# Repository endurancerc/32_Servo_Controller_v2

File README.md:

[README.md](https://github.com/user-attachments/files/35425972/README.md)
32 SERVO CONTROLLER V2 - THIS IS A WORK IN PROGRESS, POSTING FOR ANYONE THAT CARES

New Features in v2

\--------------------------------------------------------------------------------------------------------------------

Re-designed layout, better usb-c placement

STM32 dedicated servo driver (TRUE 12BIT RESOLUTION)

onboard microphone and stereo amplifiers

Full color TFT @ 324x240

Onboard GPS/GLONASS receiver

OV5640 camera support

microSD card slot on the bottom

onboard button pad (it broke during testing so i might scrap this pad. looks nice and had potential but too fragile)

Support for many I2C add on sensors. CO2, Air Quality, Thermal Camera, GPS

Runs DOOM and other silly games

Onboard Aircraft Tracker

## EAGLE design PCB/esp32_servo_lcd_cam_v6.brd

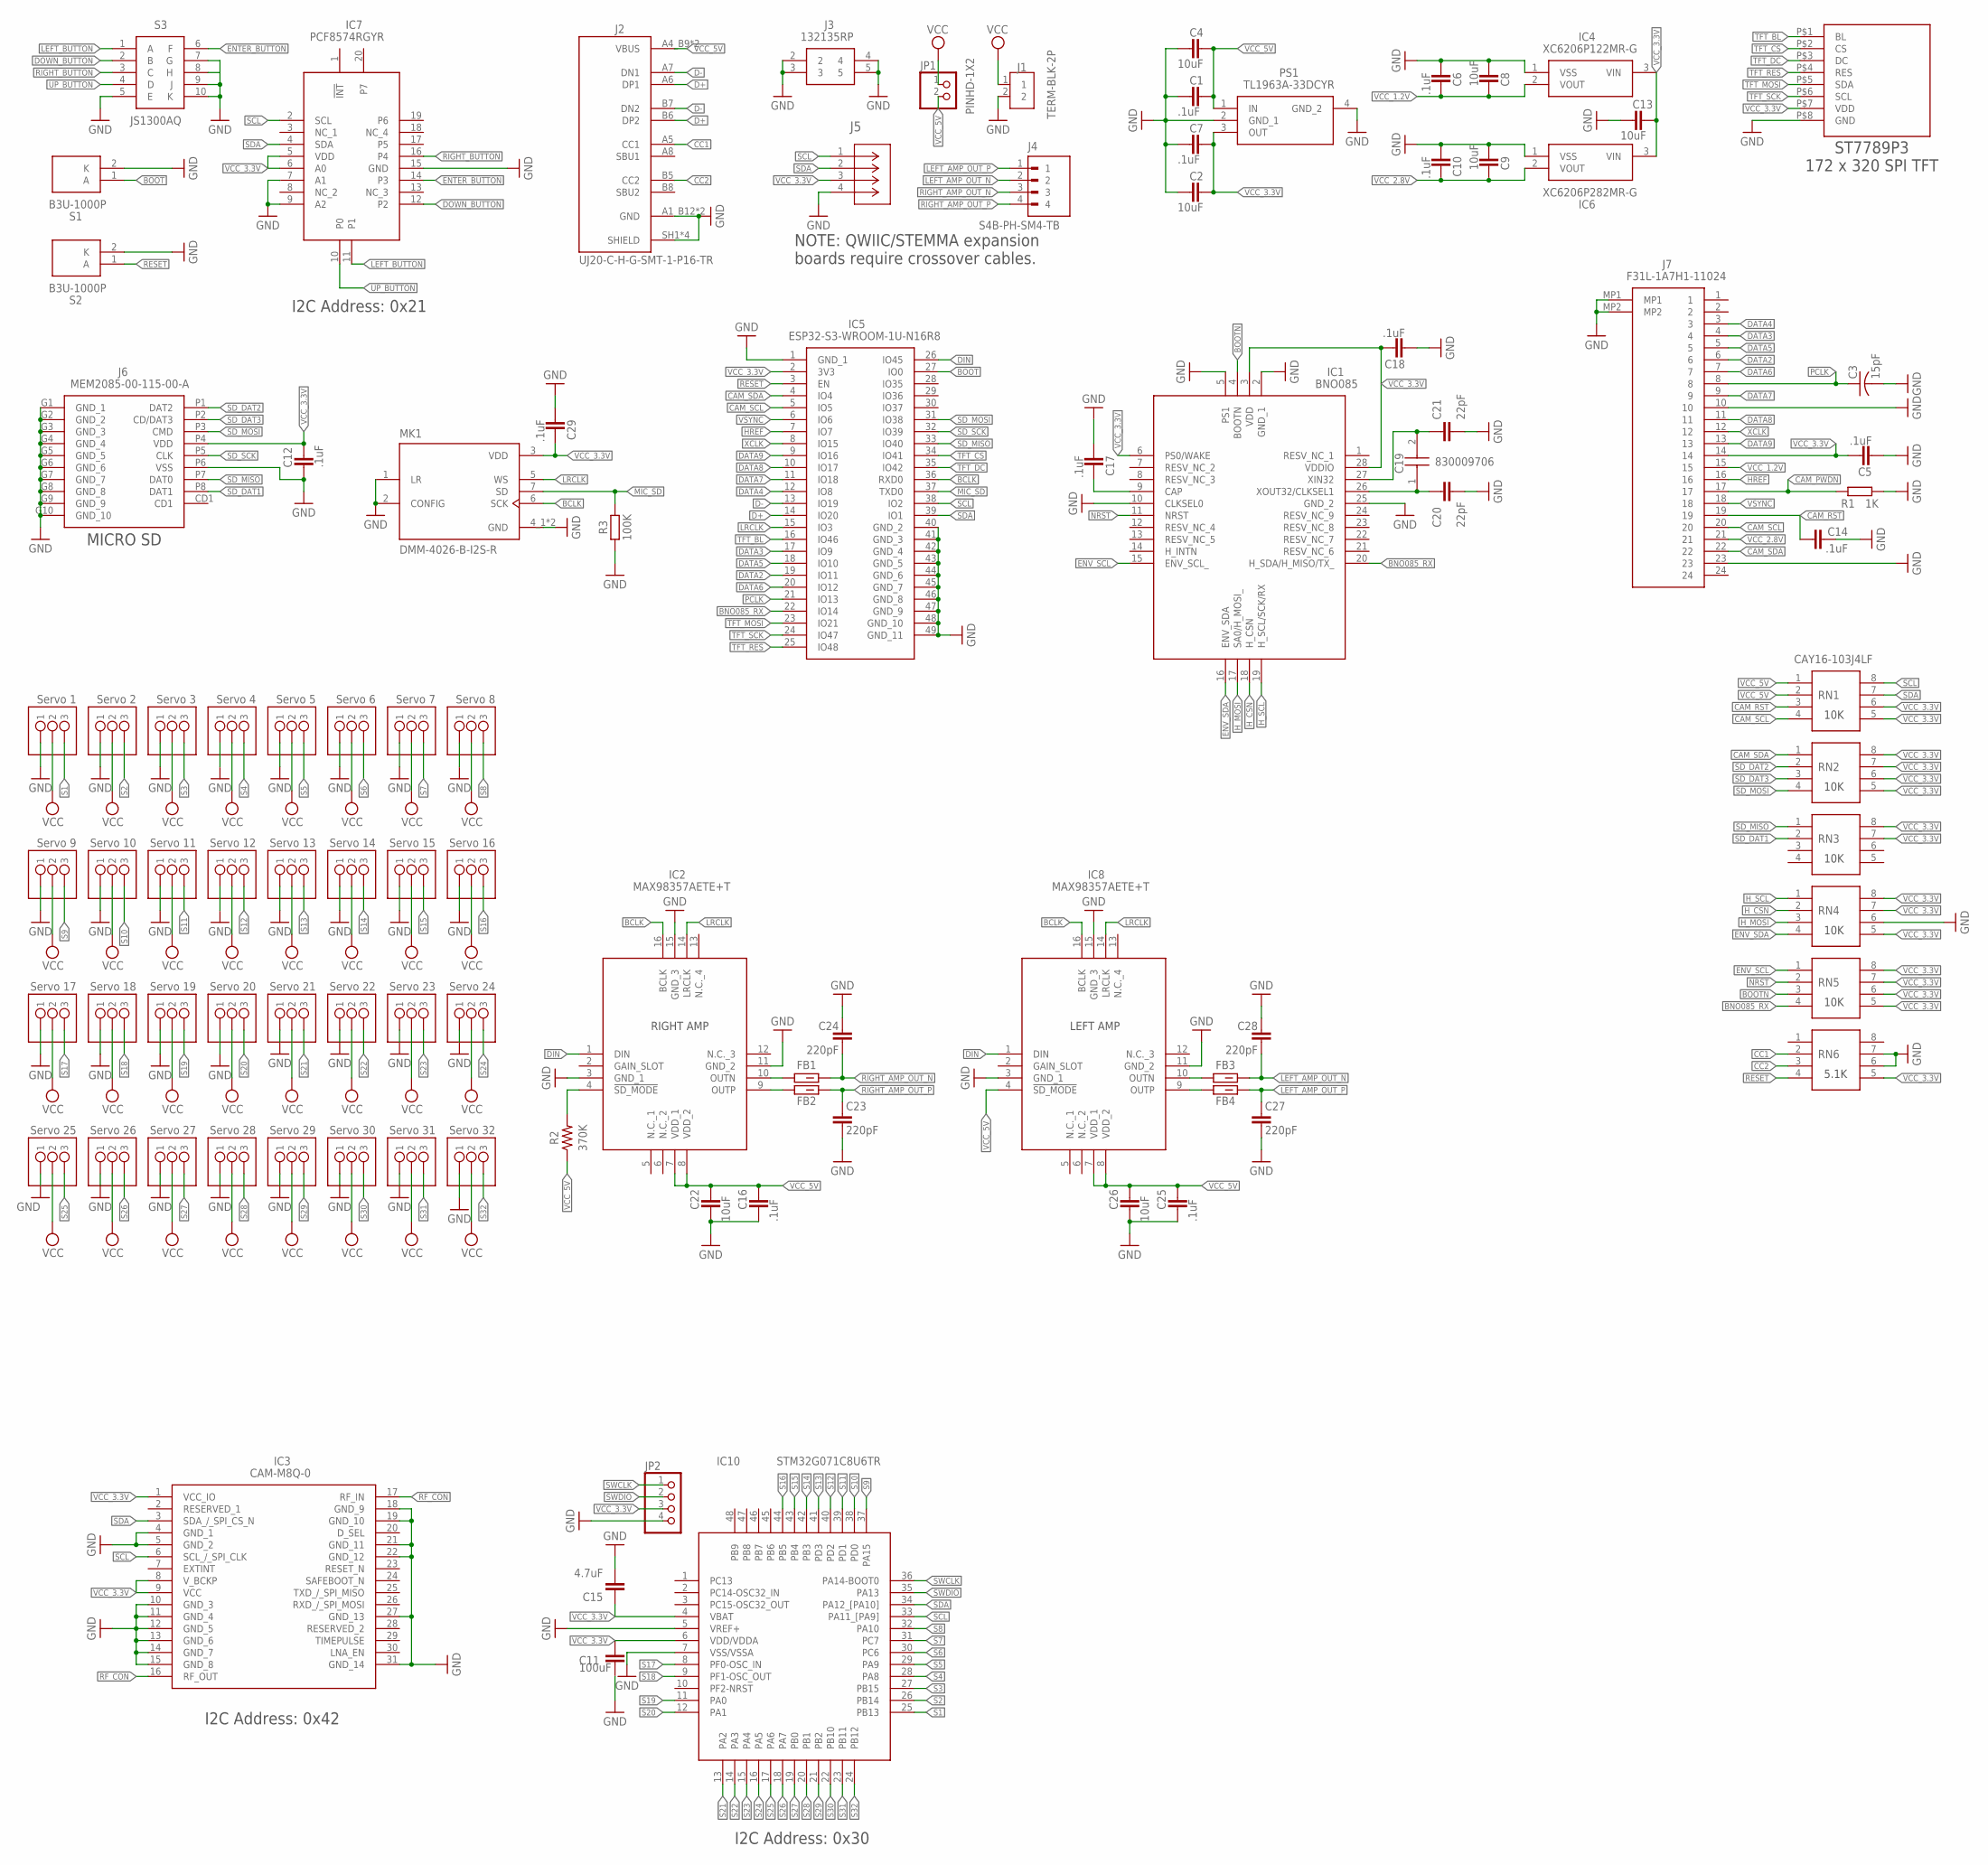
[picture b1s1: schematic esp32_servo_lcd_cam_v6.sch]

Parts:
C1, C5, C6, C7, C10, C12, C14, C16, C17, C18, C25, C29: .1uF; CAPC1110X102
C2, C4, C8, C9, C13, C22, C26: 10uF; CAPC1110X102
C3: 15pF; CAPC2012X110
C11: 100uF; CAPC3225X135
C15: 4.7uF; CAPC1005X60
C19: 830009706
C20, C21: 22pF; CAPC1005X60
C23, C24, C27, C28: 220pF; CAPC1005X60
FB1, FB2, FB3, FB4: LM18AG601; BEADC1608X95N
IC1: BNO085
IC2, IC8: MAX98357AETE+T; QFN50P300X300X80-17N
IC3: CAM-M8Q-0; CAMM8Q0
IC4: XC6206P122MR-G; SOT95P280X130-3N
IC5: ESP32-S3-WROOM-1U-N16R8; ESP32S3WROOM1UN16R8
IC6: XC6206P282MR-G; SOT95P280X130-3N
IC7: PCF8574RGYR; SN74CB3Q3244RGYR
IC10: STM32G071C8U6TR; QFN50P700X700X65-49N
J1: TERM-BLK-2P; TERMBLK_508-2N
J2: UJ20-C-H-G-SMT-1-P16-TR; SAMESKY_UJ20-C-H-G-SMT-1-P16-TR
J3: 132135RP
J4: S4B-PH-SM4-TB; JST_S4B-PH-SM4-TB
J5: SM04B-SRSS-TBCONN_SM04B-SRSS-TB_JST; CONN_SM04B-SRSS-TB_JST
J6: MEM2085-00-115-00-A; MEM20850011500A
J7: F31L-1A7H1-11024; F31L1A7H111024
JP1: PINHD-1X2; 1X02
JP2: PINHD-1X4; 1X04
MK1: DMM-4026-B-I2S-R; MIC_DMM-4026-B-I2S-R
PS1: TL1963A-33DCYR; SOT230P700X180-4N
R1: 1K; RESC1608X60
R2: 370K; RESC1608X60
R3: 100K; RESC1005X40
RN1, RN2, RN3, RN4, RN5, RN6: CAY16-103J4LF; CAY16151J4LF
S1, S2: B3U-1000P
S3: JS1300AQ; JS1300
U$1: Servo 6; 1X03
U$2: Servo 7; 1X03
U$3: Servo 8; 1X03
U$4: Servo 9; 1X03
U$5: Servo 10; 1X03
U$6: Servo 11; 1X03
U$7: Servo 12; 1X03
U$8: Servo 13; 1X03
U$9: Servo 14; 1X03
U$10: Servo 15; 1X03
U$11: Servo 4; 1X03
U$12: Servo 5; 1X03
U$13: Servo 1; 1X03
U$14: Servo 3; 1X03
U$15: Servo 2; 1X03
U$16: Servo 16; 1X03
U$17: Servo 17; 1X03
U$18: Servo 18; 1X03
U$19: Servo 19; 1X03
U$20: Servo 21; 1X03
U$21: Servo 20; 1X03
U$22: Servo 22; 1X03
U$23: Servo 23; 1X03
U$24: Servo 24; 1X03
U$25: Servo 25; 1X03
U$26: Servo 26; 1X03
U$27: Servo 27; 1X03
U$28: Servo 28; 1X03
U$29: Servo 29; 1X03
U$30: Servo 30; 1X03
U$31: Servo 31; 1X03
U$32: Servo 32; 1X03
U$33: 1.47_IN_TFT_172_320_ST7789P3

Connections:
BCLK: IC2.16 (BCLK), IC5.36 (RXD0), IC8.16 (BCLK), MK1.6 (SCK)
BNO085_RX: IC1.20 (H_SDA/H_MISO/TX_), IC5.22 (IO14), RN5.4
BOOT: IC5.27 (IO0), S1.1 (A)
BOOTN: IC1.4 (BOOTN), RN5.3
CAM_PWDN: J7.17, R1.1
CAM_RST: C14.1, J7.19, RN1.3
CAM_SCL: IC5.5 (IO5), J7.20, RN1.4
CAM_SDA: IC5.4 (IO4), J7.22, RN2.1
CC1: J2.A5 (CC1), RN6.2
CC2: J2.B5 (CC2), RN6.3
D+: IC5.14 (IO20), J2.A6 (DP1), J2.B6 (DP2)
D-: IC5.13 (IO19), J2.A7 (DN1), J2.B7 (DN2)
DATA2: IC5.19 (IO11), J7.6
DATA3: IC5.17 (IO9), J7.4
DATA4: IC5.12 (IO8), J7.3
DATA5: IC5.18 (IO10), J7.5
DATA6: IC5.20 (IO12), J7.7
DATA7: IC5.11 (IO18), J7.9
DATA8: IC5.10 (IO17), J7.11
DATA9: IC5.9 (IO16), J7.13
DIN: IC2.1 (DIN), IC5.26 (IO45), IC8.1 (DIN)
DOWN_BUTTON: IC7.12 (P2), S3.2 (B)
ENTER_BUTTON: IC7.14 (P3), S3.6 (F)
ENV_SCL: IC1.15 (ENV_SCL_), RN5.1
ENV_SDA: IC1.16 (ENV_SDA), RN4.4
GND: C1.2, C2.2, C3.2, C4.2, C5.2, C6.2, C7.2, C8.2, C9.2, C10.2, C11.2, C12.2, C13.2, C14.2, C15.2, C16.2, C17.2, C18.2, C20.2, C21.2, C22.2, C23.2, C24.2, C25.2, C26.2, C27.2, C28.2, C29.2, IC1.2 (GND_1), IC1.5 (PS1), IC1.10 (CLKSEL0), IC1.25 (GND_2), IC2.3 (GND_1), IC2.11 (GND_2), IC2.15 (GND_3), IC3.4 (GND_1), IC3.5 (GND_2), IC3.10 (GND_3), IC3.11 (GND_4), IC3.12 (GND_5), IC3.13 (GND_6), IC3.14 (GND_7), IC3.15 (GND_8), IC3.18 (GND_9), IC3.19 (GND_10), IC3.21 (GND_11), IC3.22 (GND_12), IC3.27 (GND_13), IC3.31 (GND_14), IC4.1 (VSS), IC5.1 (GND_1), IC5.40 (GND_2), IC5.41 (GND_3), IC5.42 (GND_4), IC5.43 (GND_5), IC5.44 (GND_6), IC5.45 (GND_7), IC5.46 (GND_8), IC5.47 (GND_9), IC5.48 (GND_10), IC5.49 (GND_11), IC6.1 (VSS), IC7.7 (A1), IC7.9 (A2), IC7.15 (GND), IC8.3 (GND_1), IC8.11 (GND_2), IC8.15 (GND_3), IC10.5 (VREF+), IC10.7 (VSS/VSSA), J1.2, J2.A1_B12 (GND), J2.B1_A12 (GND), J2.SH1 (SHIELD), J2.SH2 (SHIELD), J2.SH3 (SHIELD), J2.SH4 (SHIELD), J3.2, J3.3, J3.4, J3.5, J5.4, J6.G1 (GND_1), J6.G2 (GND_2), J6.G3 (GND_3), J6.G4 (GND_4), J6.G5 (GND_5), J6.G6 (GND_6), J6.G7 (GND_7), J6.G8 (GND_8), J6.G9 (GND_9), J6.G10 (GND_10), J6.P6 (VSS), J7.10, J7.23, J7.MP1, J7.MP2, JP2.4, MK1.1 (LR), MK1.2 (CONFIG), MK1.4_1 (GND), MK1.4_2 (GND), PS1.2 (GND_1), PS1.4 (GND_2), R1.2, R3.1, RN4.6, RN6.6, RN6.7, S1.2 (K), S2.2 (K), S3.5 (E), S3.7 (G), S3.8 (H), S3.9 (J), S3.10 (K), U$1.1, U$2.1, U$3.1, U$4.1, U$5.1, U$6.1, U$7.1, U$8.1, U$9.1, U$10.1, U$11.1, U$12.1, U$13.1, U$14.1, U$15.1, U$16.1, U$17.1, U$18.1, U$19.1, U$20.1, U$21.1, U$22.1, U$23.1, U$24.1, U$25.1, U$26.1, U$27.1, U$28.1, U$29.1, U$30.1, U$31.1, U$32.1, U$33.P$8 (GND)
HREF: IC5.7 (IO7), J7.16
H_CSN: IC1.18 (H_CSN), RN4.2
H_MOSI: IC1.17 (SA0/H_MOSI_), RN4.3
H_SCL: IC1.19 (H_SCL/SCK/RX), RN4.1
LEFT_AMP_OUT_N: C28.1, FB3.2, J4.2
LEFT_AMP_OUT_P: C27.1, FB4.2, J4.1
LEFT_BUTTON: IC7.11 (P1), S3.1 (A)
LRCLK: IC2.14 (LRCLK), IC5.15 (IO3), IC8.14 (LRCLK), MK1.5 (WS)
MIC_SD: IC5.37 (TXD0), MK1.7 (SD), R3.2
unnamed: FB3.1, IC8.10 (OUTN)
unnamed: FB4.1, IC8.9 (OUTP)
unnamed: IC2.4 (!SD_MODE), R2.2
unnamed: FB1.1, IC2.10 (OUTN)
unnamed: FB2.1, IC2.9 (OUTP)
unnamed: C17.1, IC1.9 (CAP)
unnamed: C19.2, C21.1, IC1.27 (XIN32)
unnamed: C19.1, C20.1, IC1.26 (XOUT32/CLKSEL1)
NRST: IC1.11 (NRST), RN5.2
PCLK: C3.1, IC5.21 (IO13), J7.8
RESET: IC5.3 (EN), RN6.4, S2.1 (A)
RF_CON: IC3.16 (RF_OUT), IC3.17 (RF_IN)
RIGHT_AMP_OUT_N: C24.1, FB1.2, J4.3
RIGHT_AMP_OUT_P: C23.1, FB2.2, J4.4
RIGHT_BUTTON: IC7.16 (P4), S3.3 (C)
S1: IC10.25 (PB13), U$13.3
S2: IC10.26 (PB14), U$15.3
S3: IC10.27 (PB15), U$14.3
S4: IC10.28 (PA8), U$11.3
S5: IC10.29 (PA9), U$12.3
S6: IC10.30 (PC6), U$1.3
S7: IC10.31 (PC7), U$2.3
S8: IC10.32 (PA10), U$3.3
S9: IC10.37 (PA15), U$4.3
S10: IC10.38 (PD0), U$5.3
S11: IC10.39 (PD1), U$6.3
S12: IC10.40 (PD2), U$7.3
S13: IC10.41 (PD3), U$8.3
S14: IC10.42 (PB3), U$9.3
S15: IC10.43 (PB4), U$10.3
S16: IC10.44 (PB5), U$16.3
S17: IC10.8 (PF0-OSC_IN), U$17.3
S18: IC10.9 (PF1-OSC_OUT), U$18.3
S19: IC10.11 (PA0), U$19.3
S20: IC10.12 (PA1), U$21.3
S21: IC10.13 (PA2), U$20.3
S22: IC10.14 (PA3), U$22.3
S23: IC10.15 (PA4), U$23.3
S24: IC10.16 (PA5), U$24.3
S25: IC10.17 (PA6), U$25.3
S26: IC10.18 (PA7), U$26.3
S27: IC10.19 (PB0), U$27.3
S28: IC10.20 (PB1), U$28.3
S29: IC10.21 (PB2), U$29.3
S30: IC10.22 (PB10), U$30.3
S31: IC10.23 (PB11), U$31.3
S32: IC10.24 (PB12), U$32.3
SCL: IC3.6 (SCL_/_SPI_CLK), IC5.38 (IO2), IC7.2 (SCL), IC10.33 (PA11_[PA9]), J5.1, RN1.8
SDA: IC3.3 (SDA_/_SPI_CS_N), IC5.39 (IO1), IC7.4 (SDA), IC10.34 (PA12_[PA10]), J5.2, RN1.7
SD_DAT1: J6.P8 (DAT1), RN3.2
SD_DAT2: J6.P1 (DAT2), RN2.2
SD_DAT3: J6.P2 (CD/DAT3), RN2.3
SD_MISO: IC5.33 (IO40), J6.P7 (DAT0), RN3.1
SD_MOSI: IC5.31 (IO38), J6.P3 (CMD), RN2.4
SD_SCK: IC5.32 (IO39), J6.P5 (CLK)
SWCLK: IC10.36 (PA14-BOOT0), JP2.1
SWDIO: IC10.35 (PA13), JP2.2
TFT_BL: IC5.16 (IO46), U$33.P$1 (BL)
TFT_CS: IC5.34 (IO41), U$33.P$2 (CS)
TFT_DC: IC5.35 (IO42), U$33.P$3 (DC)
TFT_MOSI: IC5.23 (IO21), U$33.P$5 (SDA)
TFT_RES: IC5.25 (IO48), U$33.P$4 (RES)
TFT_SCK: IC5.24 (IO47), U$33.P$6 (SCL)
UP_BUTTON: IC7.10 (P0), S3.4 (D)
VCC: J1.1, JP1.1, U$1.2, U$2.2, U$3.2, U$4.2, U$5.2, U$6.2, U$7.2, U$8.2, U$9.2, U$10.2, U$11.2, U$12.2, U$13.2, U$14.2, U$15.2, U$16.2, U$17.2, U$18.2, U$19.2, U$20.2, U$21.2, U$22.2, U$23.2, U$24.2, U$25.2, U$26.2, U$27.2, U$28.2, U$29.2, U$30.2, U$31.2, U$32.2
VCC_1.2V: C6.1, C8.1, IC4.2 (VOUT), J7.15
VCC_2.8V: C9.1, C10.1, IC6.2 (VOUT), J7.21
VCC_3.3V: C2.1, C5.1, C7.1, C11.1, C12.1, C13.1, C15.1, C18.1, C29.1, IC1.3 (VDD), IC1.6 (PS0/WAKE), IC1.28 (VDDIO), IC3.1 (VCC_IO), IC3.8 (V_BCKP), IC3.9 (VCC), IC4.3 (VIN), IC5.2 (3V3), IC6.3 (VIN), IC7.5 (VDD), IC7.6 (A0), IC10.4 (VBAT), IC10.6 (VDD/VDDA), J5.3, J6.P4 (VDD), J7.14, JP2.3, MK1.3 (VDD), PS1.3 (OUT), RN1.5, RN1.6, RN2.5, RN2.6, RN2.7, RN2.8, RN3.7, RN3.8, RN4.5, RN4.7, RN4.8, RN5.5, RN5.6, RN5.7, RN5.8, RN6.5, U$33.P$7 (VDD)
VCC_5V: C1.1, C4.1, C16.1, C22.1, C25.1, C26.1, IC2.7 (VDD_1), IC2.8 (VDD_2), IC8.4 (!SD_MODE), IC8.7 (VDD_1), IC8.8 (VDD_2), J2.A4_B9 (VBUS), J2.B4_A9 (VBUS), JP1.2, PS1.1 (IN), R2.1, RN1.1, RN1.2
VSYNC: IC5.6 (IO6), J7.18
XCLK: IC5.8 (IO15), J7.12

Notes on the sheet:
ST7789P3 172 x 320 SPI TFT
MICRO SD
I2C Address: 0x21
NOTE: QWIIC/STEMMA expansion boards require crossover cables.
I2C Address: 0x42
I2C Address: 0x30
10K
5.1K
RIGHT AMP
LEFT AMP

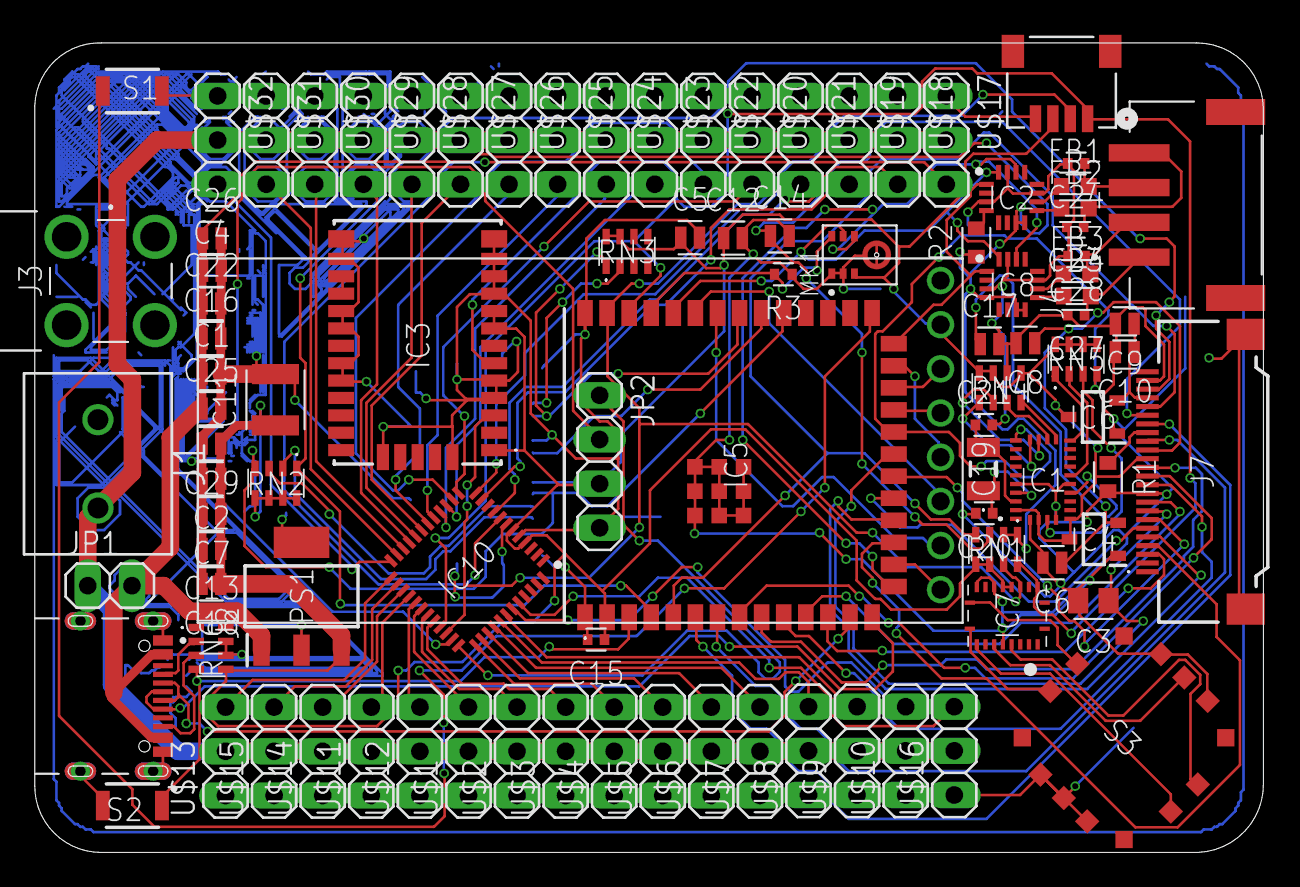
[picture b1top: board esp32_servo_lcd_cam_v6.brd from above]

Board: 2 copper layers, 70.7 x 46.6 mm, 98 parts (1 on the bottom side), 106 nets.

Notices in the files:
parts and their libraries:
COPYRIGHT: Copyright (C) 2026 Ultra Librarian. All rights reserved.
